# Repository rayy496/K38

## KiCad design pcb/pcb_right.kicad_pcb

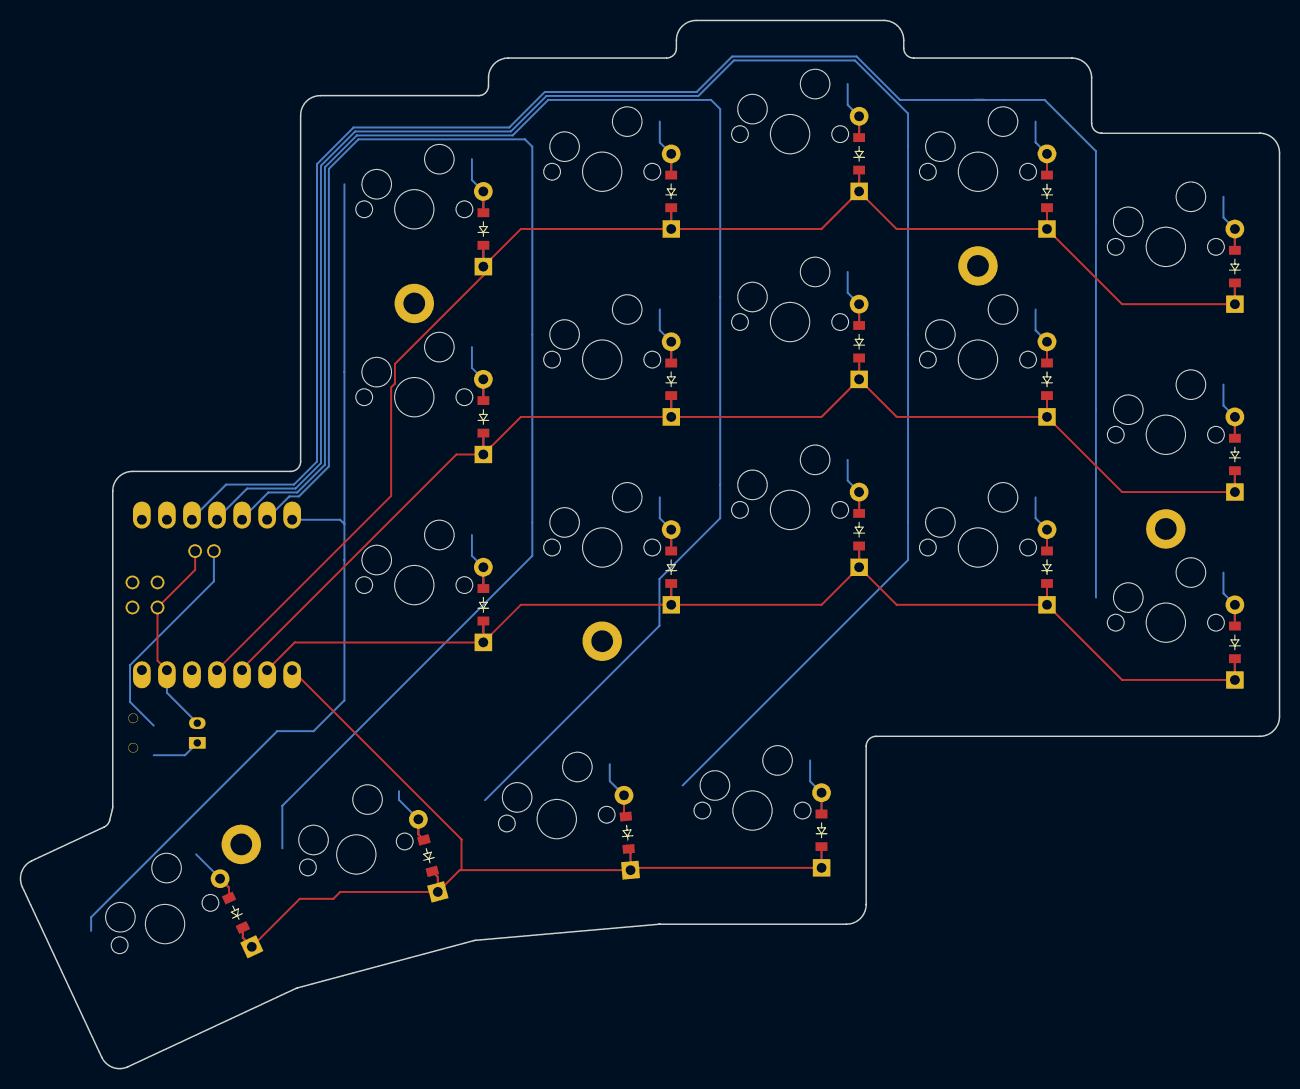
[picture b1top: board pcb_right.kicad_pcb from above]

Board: 2 copper layers, 127.7 x 106.3 mm, 41 parts (0 on the bottom side), 31 nets.

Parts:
D1, D2, D3, D4, D5, D6, D7, D8, D9, D10, D11, D12, D13, D14, D15, D16, D17, D18, D19: ComboDiode
JST1: JST_PH_S2B-PH-K_02x2.00mm_Angled
S1, S2, S3, S4, S5, S6, S7, S8, S9, S10, S11, S12, S13, S14, S15, S16, S17, S18, S19: MX
T1: SPDT_C128955
_1: xiao-ble

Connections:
GND: JST1.2, _1.2, _1.9, _1.22
P2: S1.1, S2.1, S3.1, _1.16
P3: S4.1, S5.1, S6.1, S16.1, _1.15
P4: S7.1, S8.1, S9.1, S17.1, _1.14
P5: S10.1, S11.1, S12.1, S18.1, _1.13
P6: S13.1, S14.1, S15.1, S19.1, _1.12
P7: D16.1, D17.1, D18.1, D19.1, _1.7
P8: D1.1, D4.1, D7.1, D10.1, D13.1, _1.6
P9: D2.1, D5.1, D8.1, D11.1, D14.1, _1.5
P10: D3.1, D6.1, D9.1, D12.1, D15.1, _1.4
RAW: T1.2, _1.21
mirror_c1_r1: D1.2, S1.2
mirror_c1_r2: D2.2, S2.2
mirror_c1_r3: D3.2, S3.2
mirror_c2_r1: D4.2, S4.2
mirror_c2_r2: D5.2, S5.2
mirror_c2_r3: D6.2, S6.2
mirror_c3_r1: D7.2, S7.2
mirror_c3_r2: D8.2, S8.2
mirror_c3_r3: D9.2, S9.2
mirror_c4_r1: D10.2, S10.2
mirror_c4_r2: D11.2, S11.2
mirror_c4_r3: D12.2, S12.2
mirror_c5_r1: D13.2, S13.2
mirror_c5_r2: D14.2, S14.2
mirror_c5_r3: D15.2, S15.2
mirror_t1_r: D16.2, S16.2
mirror_t2_r: D17.2, S17.2
mirror_t3_r: D18.2, S18.2
mirror_t4_r: D19.2, S19.2
pos: JST1.1, T1.1

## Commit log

2026-01-02 add Xiao footprint for ergogen
2026-01-03 Added config.yaml and footprint files for Xiao and mounting hole.
2026-01-03 fix config.yaml file name
2026-01-08 add pcb complete files
2026-01-09 add zmk-config file
2026-01-19 add ergogen output files
2026-01-19 add gitignore
